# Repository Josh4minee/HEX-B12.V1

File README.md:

##

# HEX-B12.V1
HEX-B12.V120 is a custom-designed hexapod using MG996R servos. Its theme is based on the beloved bot B-12 from the popular video game [Stray](https://en.wikipedia.org/wiki/Stray_(video_game)). It is inspired by the Make Your Pet project and is powered by a custom inverse kinematics-based algorithm.

The mechanical part dimensions are inspired by the [Make Your Pet](https://www.makeyourpet.com/) Chipo project; everything else is custom-made by me.

# Information
Consult the following based on your needs:
- [Hexapod](#hexapod)
- [Remote](#remote)
- [Printing](#printing)
- [Wiring diagram](#wiring-diagram)
- [Hexapod Assembly](#hexapod-assembly)
- [Hexapod pictures and videos](#hexapod-pictures-and-videos)
- [Pre-powering on precautions](#pre-powering-on-precautions)
- [Remote Assembly](#remote-assembly)
- [How to use the remote](#how-to-use-the-remote)
- [Sources](#sources)
- [License](#license)

# Hexapod

Why I made this hexapod is because since I was young I have always wanted to build "stuff", making robots was always very appealing to me and this project is simpler than a quadruped yet just as fun for a beginner like me and I hope the people that come across this project like it! It is worth mentionning that this is also a college project hense why I have put so much time and effort on it in such a short ammount of time.

As per the title, this hexapod uses MG996R servos, this decision was made because of cost, any other servo is 3x to 4x the price of these ones.

The power system consists of one big 5200mAh 2S lipo battery for optimal opperation time, three UBECs for stable 7v to 5v conversion and one 10A manual reset fuse.

An arduino nano was used as the brains of this project simply because it was a requirement from my college and it is thanfully fast enough for its use case.

An [Adafruit PCA9685](https://learn.adafruit.com/16-channel-pwm-servo-driver/overview) servo driver was chosen to controll the huge amount fof servos this robot requires.

The nRF24L01+PA+LNA modules were chosen for wireless communication, the power emplified version was used for its antenna (to keep the resemblance of [B-12](https://stray.fandom.com/wiki/B-12)) and for its range.

Finally, relays were added for ease of use and safety, like only turning on the servos 5s after the battery is pluged in.

# Remote

The main reason the remote was made is because I did not want to work with bluetooth or web based control. 

Making a remote seemed more interesting anyways and it allowed me to design my very first custom PCB:

I ended up making 2 versions because I tried to directly hook up an NRF module on the first version, this ended up failing to I just made a custom footprint for the NRF module power boards.

# Printing

The following are the settings used to print this hexapod:

- 15% grid infill everywhere, 0.28mm height and 3 walls on every part except for the 0.16mm servo shields to keep them smooth.
- Every STL file is pre-oriented and ready to print, the only parts requiring support material are the top plate, the shields, the coxa and femur horn parts, the guides. Any additional supports are not usefull.
- Printing the remote uses the same settings and the files are also pre-oriented, only the mid plate requires supports.
- The number of parts needed to be printed is indicated at the end of the names of every STL file.
- All STL files can be found the the [STL](./STL) folder.

# Wiring diagram

Here you can find the wiring diagram, component placements, and an IRL example of the completed build.
<div>

<div>
  
# Hexapod assembly
- [Coxa](./pictures/coxa_page_1.jpg)
- [Femur](./pictures/femur_page_1.jpg)
- [Tibia](./pictures/tibia_page_1.jpg)
- [Leg](./pictures/LEG_left_page_1.jpg)
- [Mid Frame](./pictures/mid_frame_page_1.jpg)
- [Frame and Legs](./pictures/frampluslegs_page_1.jpg)
- [Hexapod](./pictures/hexapod_page_1.jpg)
- [Electronics Mounting](./pictures/electronics_mounting_page_1.jpg)
- [Servo pinouts](./pictures/servo_order.png)

**NOTE: ALL SERVOS MUST BE SET TO 90 PRIOR TO ANY ASSEMBLY**

**NOTE: KEEP IN MIND THAT 3 OF THESE LEGS ARE FLIPPED**

**NOTE: DO NOT FORGET THE 18 FRICTION CAP RINGS**

The above document provides a visual on how parts are assembled, to assemble this in real life you must follow the [Frame and Legs](./pictures/frampluslegs_page_1.jpg) and [Hexapod](./pictures/hexapod_page_1.jpg) technical drawings. The order of operations is very important here, so making sure proper understanding is acquired before continuing is mandatory.

For screw sizes needed:
- Every screw needed to attach a servo is M3 35mm.
- Every screw needed to clamp together femur/coxa parts is M3 25mm.
- Every screw that holds down the friction caps is M2 10mm.
- Every other screw is M2 8mm.
- Follow [this](./pictures/Hexapod_Heated_Insert_placements.png) diagram for M2 heat insert assembly.

Follow [this](./pictures/leg_orientations.png) technical drawing for proper leg orientation assembly.

It is very recommended to apply sillicone based grease between the friction caps and legs to prevent plastic wear.

# Hexapod pictures and videos

Here is what the robot should look like once fully assembled:

Here is what the remote should look like once fully assembled:

Here is a video demonstrating the functionalities of the hexapod:

<video width="500" controls>
  <source src="hexapod.mp4" type="video/mp4">
</video>

# Pre-powering on precautions

- Make sure the legs of the hexapod are clear of any obstacles.
- Make sure all the legs are **RESTING** on the ground, the hexapod should **NOT** be standing.
- After plugging in the battery, the hexapod will enter a 10 second timer before entering its start animation.

# Remote assembly

Start by buying the PCB on [JLCPCB.](https://cart.jlcpcb.com/quote?stencilLayer=2&stencilWidth=100&stencilLength=100&stencilCounts=5&plateType=1&spm=Jlcpcb.Homepage.1010) by simply drag and droping the [gerber](PCB/HEX_remote_GERBERS.zip) files.

Once you have received and soldered your PCB, follow the diagram to assemble the remote, every screw used is M2 8mm.

# How to use the remote

The remote has 3 buttons, 2 knobs, and a joystick.
The lower knob is for global height offset, the upper knob is used to control which mode the user is in, and the 3 buttons are for 3 different states in these modes:

- Normal walking mode: the hexapod turns and follows the joystick’s direction. Each button selects the current walking GAIT: 1 for tripod, 2 for ripple, and 3 is actually an Easter egg.

- Crab mode: the hexapod follows joystick directions without ever turning its body. The GAIT selection is the same as above.

- Body control mode: here you can control the hexapod body. Button 1 is for planar offset mode, button 2 is for XY rotation offset mode, and button 3 is for Z rotation mode.

- Animation mode: in this mode, 3 animations can be selected using the 3 buttons.

# Sources

Huge thanks to to [MYP](https://www.makeyourpet.com/) for the inspiration and just overall help their discord community provided to this project!

Here is a list of every model I used from GrabCad to display electronic components and screws in my assem,blies:

- [All M3-M2 screws](https://grabcad.com/library/m2-metric-socket-cap-head-screws-1)
- [M3 square nuts](https://www.traceparts.com/en/product/din-square-nut?CatalogPath=TRACEPARTS%3ATP01001007016&Product=10-11062001-225045)
- [NRF anttenna module and powe board](https://github.com/KrishnaHariharan/NRF24-Breakout-Board)
- [NRF anttenna module and powe board](https://github.com/Ahsayn/nRF24-Breakout)
- [MG996R servo & servo horns](https://grabcad.com/library/mg996r-servo-3)
- [UBEC](https://grabcad.com/library/ubec-5v-5a-1)
- [Lipo alarm](https://grabcad.com/library/1-8s-lipo-li-ion-fe-battery-voltage-2in1-tester-1)
- [PCA servo driver](https://grabcad.com/library/pca9685-8)
- [Double relay](https://grabcad.com/library/2ph63091a-2-channel-5v-relay-module-1)

# License
[License](LICENSE)

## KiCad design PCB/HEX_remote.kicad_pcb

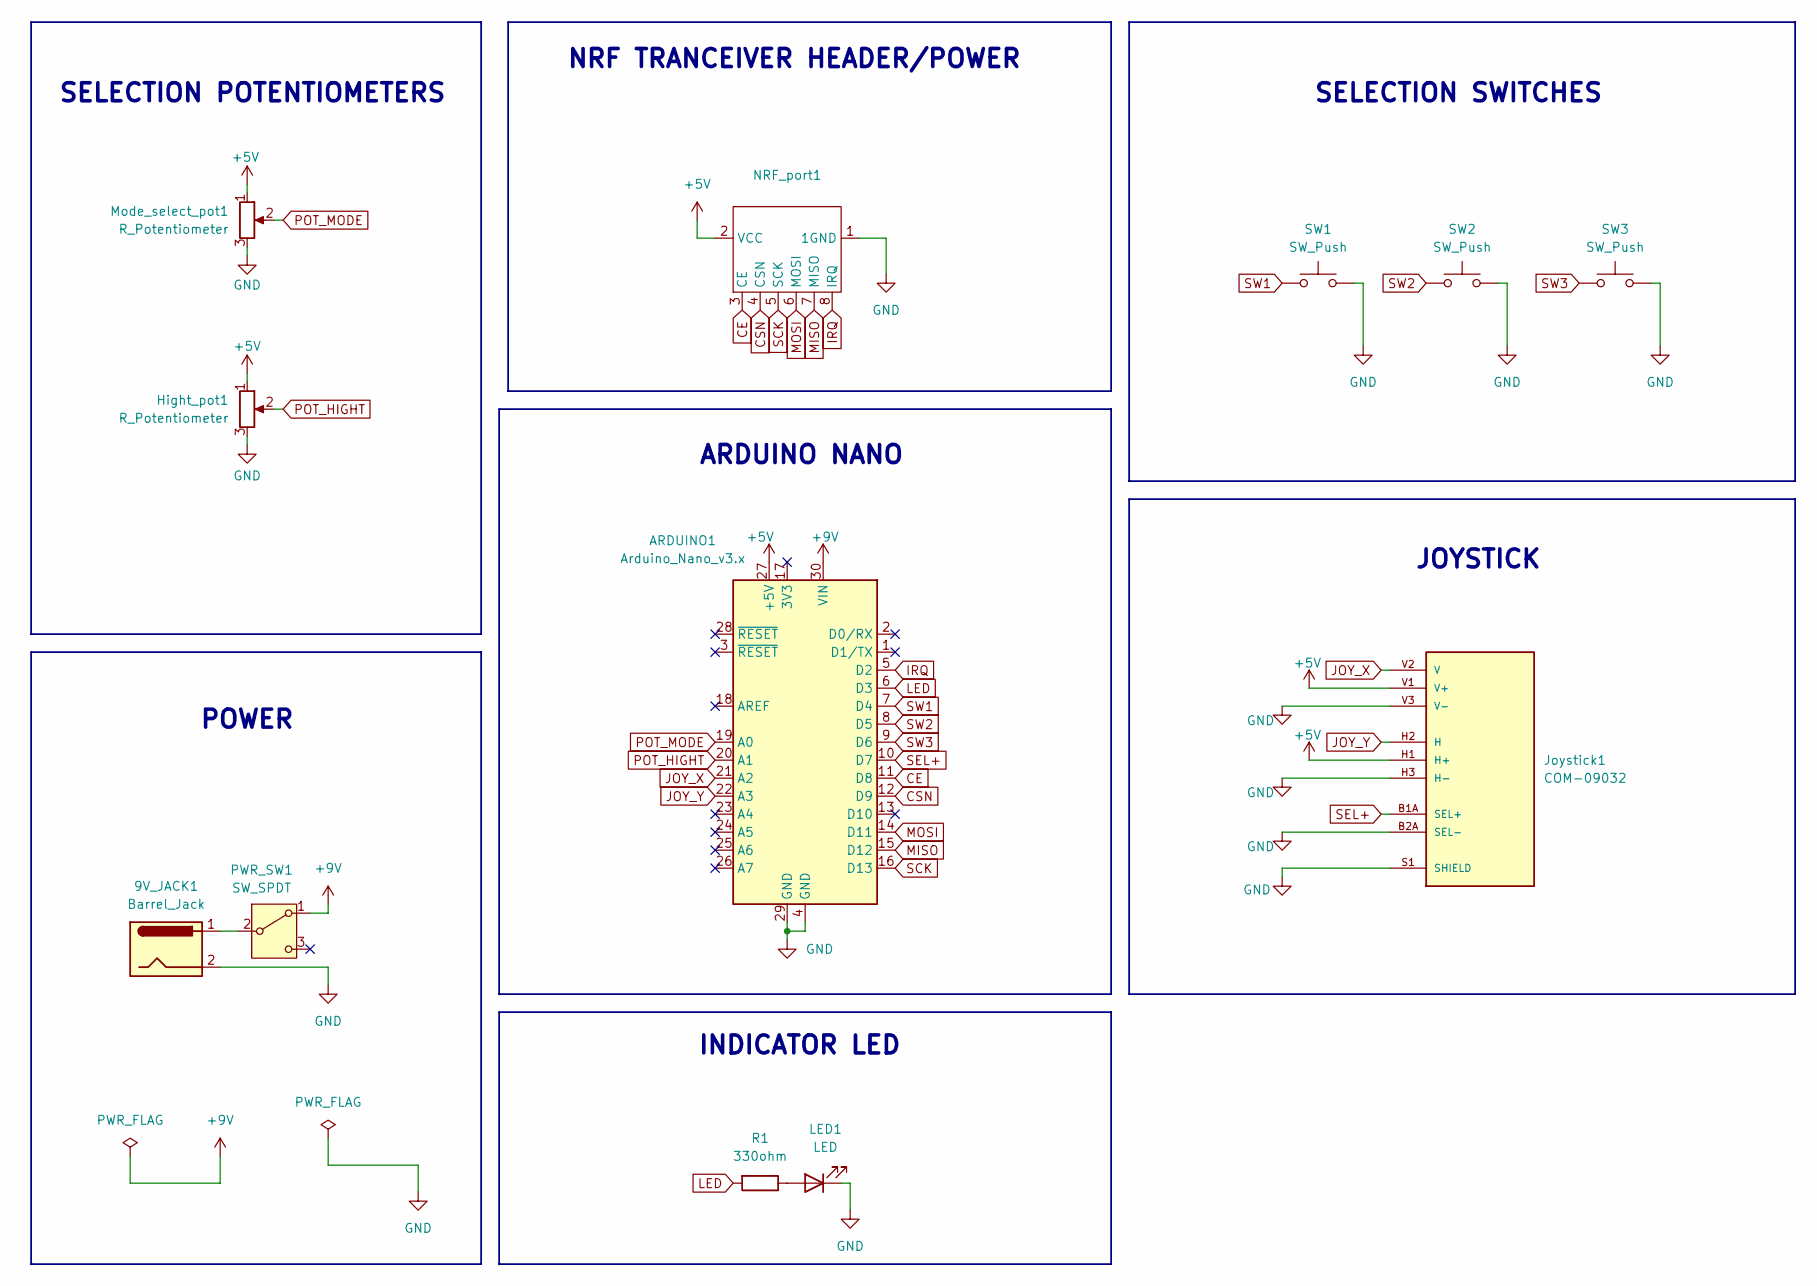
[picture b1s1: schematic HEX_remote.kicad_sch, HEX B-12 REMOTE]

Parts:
9V_JACK1: Barrel_Jack; BarrelJack_GCT_DCJ200-10-A_Horizontal
ARDUINO1: Arduino_Nano_v3.x; Arduino_Nano
Hight_pot1: R_Potentiometer; Potentiometer_Alps_RK09K_Single_Vertical
Joystick1: COM-09032; XDCR_COM-09032; PARTREV N/A
LED1: LED; LED_D5.0mm
Mode_select_pot1: R_Potentiometer; Potentiometer_Alps_RK09K_Single_Vertical
NRF_port1: NRF_ADAPTER_FOOTPRINT
PWR_SW1: SW_SPDT; SW_Slide-03_Wuerth-WS-SLTV_10x2.5x6.4_P2.54mm
R1: 330ohm; R_Axial_DIN0204_L3.6mm_D1.6mm_P7.62mm_Horizontal
SW1, SW2, SW3: SW_Push; SW_PUSH_6mm

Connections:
+5V: ARDUINO1.27 (+5V), Hight_pot1.1, Joystick1.H1 (H+), Joystick1.V1 (V+), Mode_select_pot1.1, NRF_port1.2 (VCC)
+9V: ARDUINO1.30 (VIN), PWR_SW1.1 (A)
CE: ARDUINO1.11 (D8), NRF_port1.3 (CE)
CSN: ARDUINO1.12 (D9), NRF_port1.4 (CSN)
GND: 9V_JACK1.2, ARDUINO1.4 (GND), ARDUINO1.29 (GND), Hight_pot1.3, Joystick1.B2A (SEL-), Joystick1.H3 (H-), Joystick1.S1 (SHIELD), Joystick1.S2 (SHIELD), Joystick1.S3 (SHIELD), Joystick1.S4 (SHIELD), Joystick1.V3 (V-), LED1.1 (K), Mode_select_pot1.3, NRF_port1.1 (1GND), SW1.2, SW2.2, SW3.2
IRQ: ARDUINO1.5 (D2), NRF_port1.8 (IRQ)
JOY_X: ARDUINO1.21 (A2), Joystick1.V2 (V)
JOY_Y: ARDUINO1.22 (A3), Joystick1.H2 (H)
LED: ARDUINO1.6 (D3), R1.2
MISO: ARDUINO1.15 (D12), NRF_port1.7 (MISO)
MOSI: ARDUINO1.14 (D11), NRF_port1.6 (MOSI)
unnamed: LED1.2 (A), R1.1
unnamed: 9V_JACK1.1, PWR_SW1.2 (B)
POT_HIGHT: ARDUINO1.20 (A1), Hight_pot1.2
POT_MODE: ARDUINO1.19 (A0), Mode_select_pot1.2
SCK: ARDUINO1.16 (D13), NRF_port1.5 (SCK)
SEL+: ARDUINO1.10 (D7), Joystick1.B1A (SEL+)
SW1: ARDUINO1.7 (D4), SW1.1
SW2: ARDUINO1.8 (D5), SW2.1
SW3: ARDUINO1.9 (D6), SW3.1

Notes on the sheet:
SELECTION SWITCHES
NRF TRANCEIVER HEADER/POWER
SELECTION POTENTIOMETERS
ARDUINO NANO
JOYSTICK
POWER
INDICATOR LED

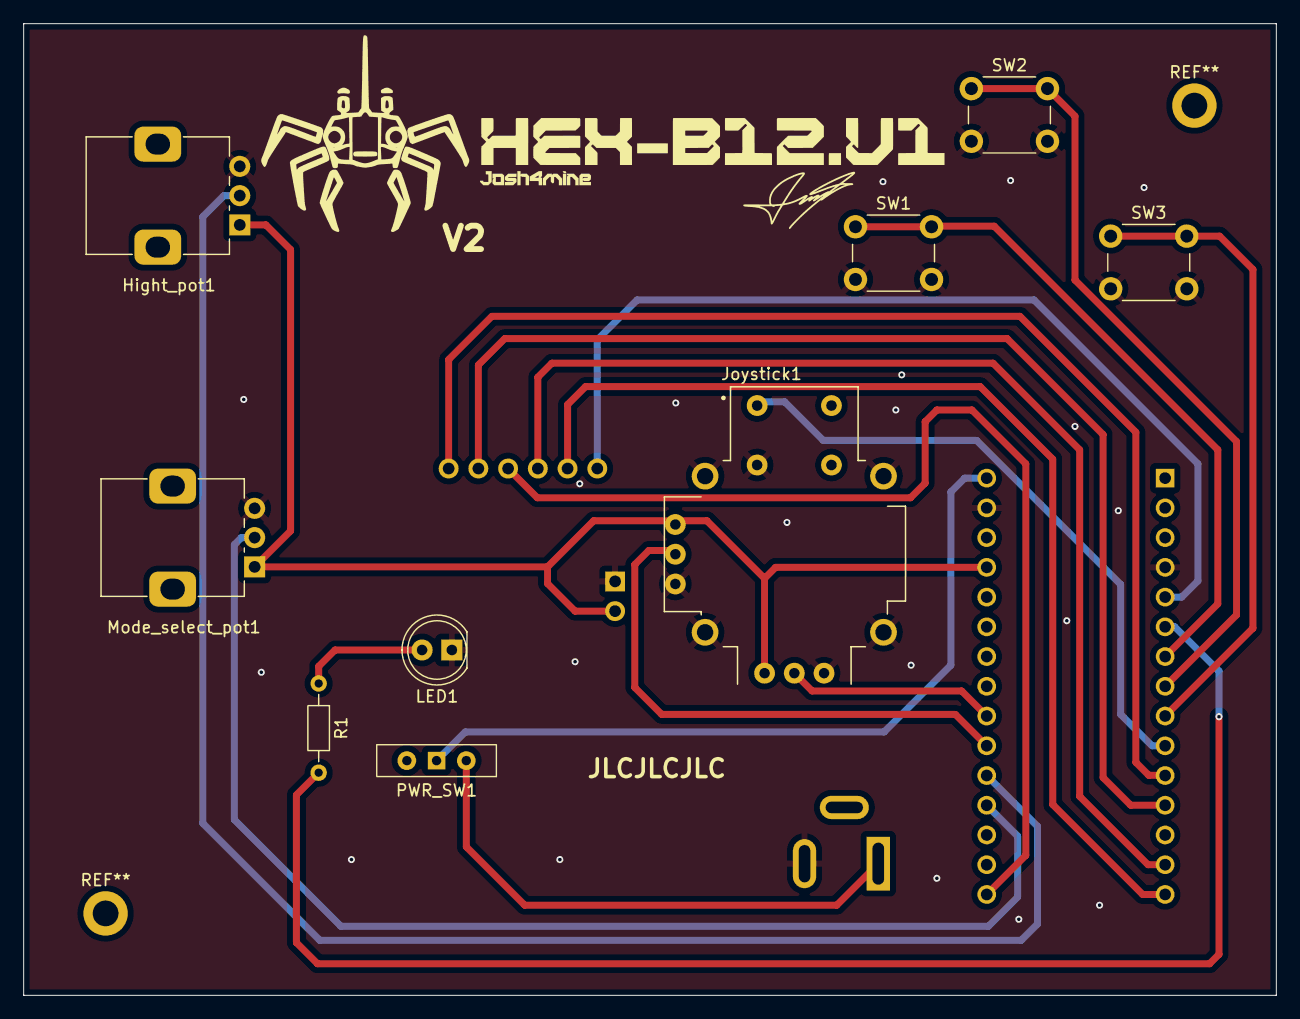
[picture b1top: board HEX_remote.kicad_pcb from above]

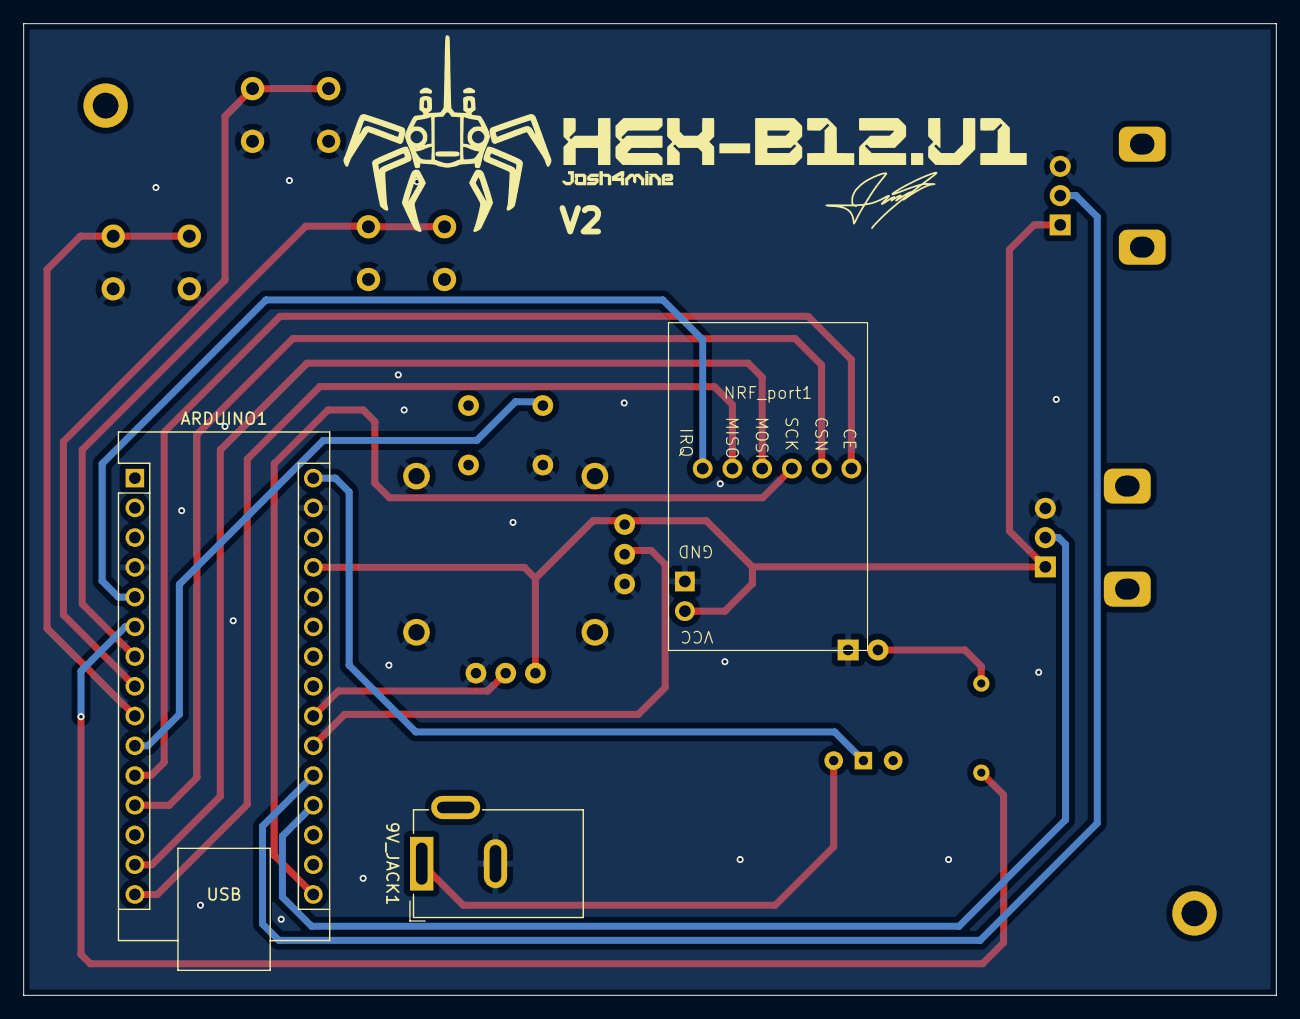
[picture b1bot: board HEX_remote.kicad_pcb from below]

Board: 2 copper layers, 107.0 x 83.0 mm, 12 parts (2 on the bottom side), 20 nets.

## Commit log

2026-04-11 Create pic
2026-04-12 Update pic
2026-04-13 Create LICENSE
2026-04-13 LICENSE
2026-04-17 Create test
2026-04-17 Update and rename test to BOM link
2026-04-17 Update BOM link
2026-04-17 Rename BOM link.txt to BOM link
2026-04-17 Rename cap x18.stl to friction cap x18.stl
2026-04-17 Rename servo order.png to servo_order.png
